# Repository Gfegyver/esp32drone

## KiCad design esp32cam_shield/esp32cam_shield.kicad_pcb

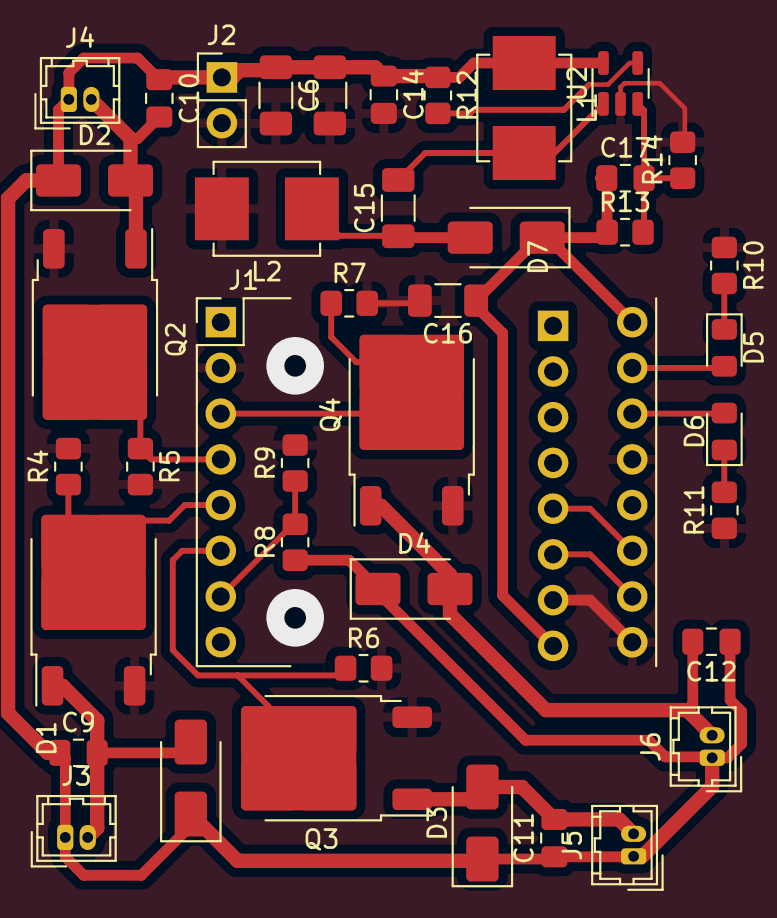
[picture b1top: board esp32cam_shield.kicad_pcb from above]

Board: 2 copper layers, 42 parts (1 on the bottom side), 22 nets.

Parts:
C6, C13, C15, C16: 10u; C_1206_3216Metric_Pad1.33x1.80mm_HandSolder
C9, C10, C11, C12: 1u; C_0805_2012Metric_Pad1.18x1.45mm_HandSolder
C14: 100n; C_0805_2012Metric_Pad1.18x1.45mm_HandSolder
C17: 2.2n; C_0805_2012Metric_Pad1.18x1.45mm_HandSolder
D1, D2, D3, D4: D; D_SMA
D5, D6: LED; LED_0805_2012Metric_Pad1.15x1.40mm_HandSolder
D7: D_Schottky; D_SMA
J1: ESP32 CAM; PinHeader_2x08_P2.54mm_Vertical
J2: Battery; PinHeader_1x02_P2.54mm_Vertical
J3, J4, J5, J6: Motor; Hirose_DF13-02P-1.25DSA_1x02_P1.25mm_Vertical
J7: Conn_01x08; PinSocket_1x08_P2.54mm_Vertical
L1, L2: 6.8uH; L_Murata_LQH55DN_5.7x5.0mm
Q1, Q2, Q3, Q4: NMOS; TO-252-2
R4, R5, R6, R7: 10k; R_0805_2012Metric_Pad1.20x1.40mm_HandSolder
R8, R9: 56kR; R_0805_2012Metric_Pad1.20x1.40mm_HandSolder
R10, R11: 200R; R_0805_2012Metric_Pad1.20x1.40mm_HandSolder
R12: 100k; R_0805_2012Metric_Pad1.20x1.40mm_HandSolder
R13: 9.1k; R_0805_2012Metric_Pad1.20x1.40mm_HandSolder
R14: 5.6k; R_0805_2012Metric_Pad1.20x1.40mm_HandSolder
U2: LMR62421XMF; SOT-23-5

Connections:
+3V3: C16.1, C17.1, D7.1 (K), J1.16, J7.8, R13.1
/GPIO0: D6.2 (A), J1.14
/GPIO1: J1.10, J7.6
/GPIO2 ADC: J1.7, R8.2, R9.1
/GPIO3: J1.11, J7.5
/GPIO12: J1.3, Q4.2 (G), R7.1
/GPIO13: J1.4, Q2.2 (G), R5.1
/GPIO14: J1.6, Q3.2 (G), R6.1
/GPIO15: J1.5, Q1.2 (G), R4.1
/GPIO16: D5.2 (A), J1.15
GND: C6.2, C13.2, C14.2, C16.2, J1.2, J1.9, J1.13, J2.2, J7.7, L2.2, Q1.3 (S), Q2.3 (S), Q3.3 (S), Q4.3 (S), R4.2, R5.2, R6.2, R7.2, R9.2, R10.1, R11.1, R14.2, U2.2 (GND)
unnamed: C9.2, D1.2 (A), J3.2, Q1.1 (D)
unnamed: C10.2, D2.2 (A), J4.2, Q2.1 (D)
unnamed: C11.2, D3.2 (A), J5.2, Q3.1 (D)
unnamed: C12.2, D4.2 (A), J6.2, Q4.1 (D)
unnamed: D5.1 (K), R10.2
unnamed: D6.1 (K), R11.2
unnamed: C15.1, D7.2 (A), L2.1
unnamed: R12.2, U2.4 (EN)
unnamed: C17.2, R13.2, R14.1, U2.3 (FB)
unnamed: C15.2, L1.2, U2.1 (SW)
VCC: C6.1, C9.1, C10.1, C11.1, C12.1, C13.1, C14.1, D1.1 (K), D2.1 (K), D3.1 (K), D4.1 (K), J2.1, J3.1, J4.1, J5.1, J6.1, L1.1, R8.1, R12.1, U2.5 (VIN)

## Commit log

2023-03-09 Kesz kapcsolas SMD MPU-6050-nel
2023-03-09 MPU-6050 modul
2023-03-10 PCB Design DONE.
